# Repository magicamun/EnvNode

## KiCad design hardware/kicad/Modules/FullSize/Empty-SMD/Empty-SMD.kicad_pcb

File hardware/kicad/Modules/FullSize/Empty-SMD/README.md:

# EnvNode FullSize SMD Module Template

This KiCad project is the 38 mm × 64 mm starting point for a Revision 0.3 FullSize daughterboard with a bottom-mounted SMD module connector.

Copy the complete directory when starting a module. Do not add application circuitry to the template itself. Preserve the 2 × 7 connector mapping, connector axis 6.35 mm from the top edge, 2.7 mm M2.5 support holes at 27 mm and 59 mm, and the reference module-identification EEPROM circuit.

See the [module-interface hardware specification](../../../../../docs/EnvNode_Module_Interface_Hardware_Specification.md) and rerun ERC and DRC on every derived board.

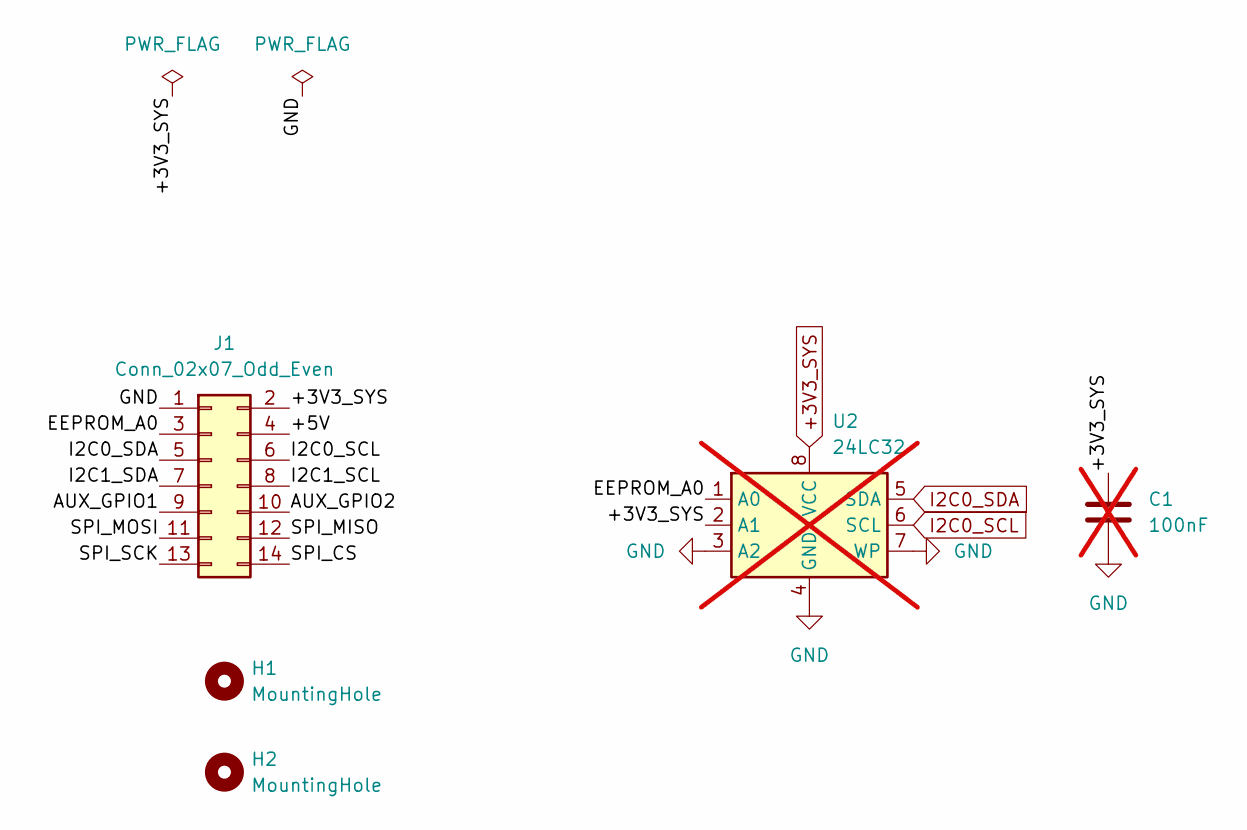
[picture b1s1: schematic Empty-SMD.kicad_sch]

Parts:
C1: 100nF; C_1206_3216Metric_Pad1.33x1.80mm_HandSolder; not fitted
H1, H2: MountingHole; MountingHole_2.7mm_M2.5_DIN965
J1: Conn_02x07_Odd_Even; J_Wurth_WR-PHD_61031421121
U2: 24LC32; SOIC-8_3.9x4.9mm_P1.27mm; not fitted

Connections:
+3V3_SYS: C1.1, J1.2, U2.2 (A1), U2.8 (VCC)
/+5V: J1.4
/AUX_GPIO1: J1.9
/AUX_GPIO2: J1.10
/EEPROM_A0: J1.3, U2.1 (A0)
/I2C1_SCL: J1.8
/I2C1_SDA: J1.7
/SPI_CS: J1.14
/SPI_MISO: J1.12
/SPI_MOSI: J1.11
/SPI_SCK: J1.13
GND: C1.2, J1.1, U2.3 (A2), U2.4 (GND), U2.7 (WP)
I2C0_SCL: J1.6, U2.6 (SCL)
I2C0_SDA: J1.5, U2.5 (SDA)

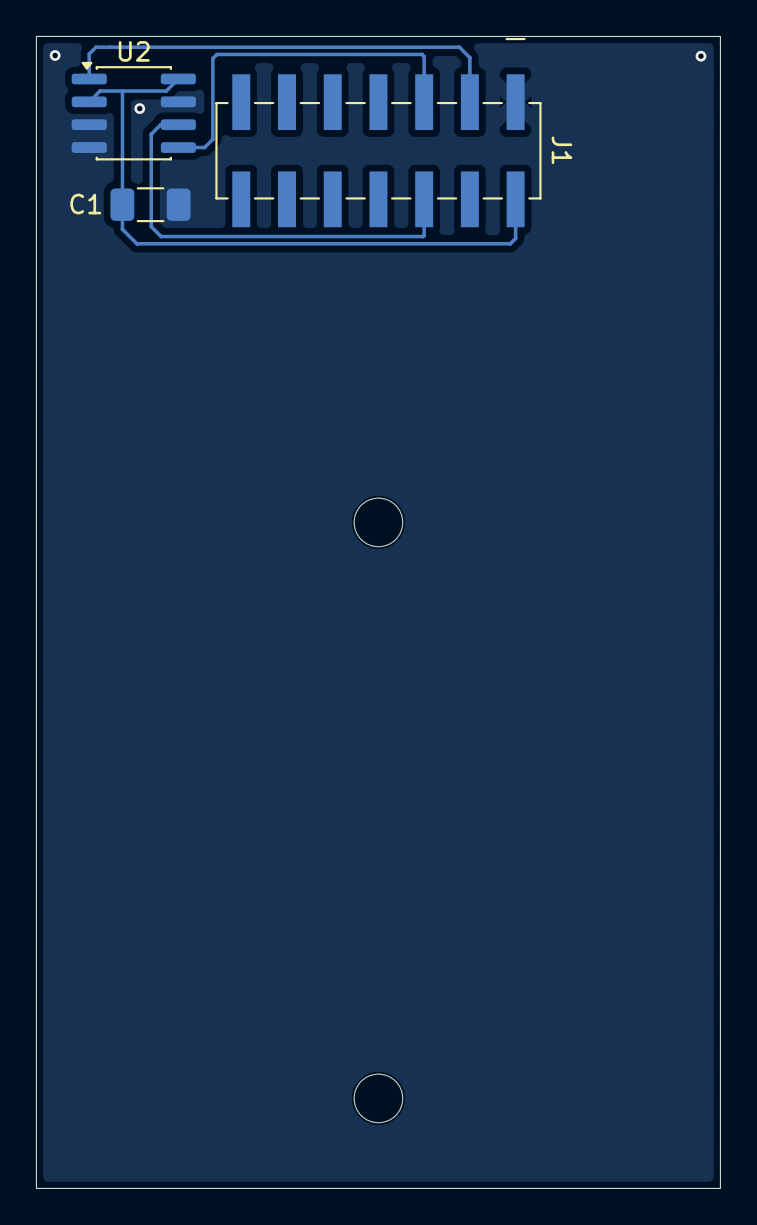
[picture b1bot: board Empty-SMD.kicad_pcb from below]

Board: 2 copper layers, 38.0 x 64.0 mm, 5 parts (3 on the bottom side), 5 nets.

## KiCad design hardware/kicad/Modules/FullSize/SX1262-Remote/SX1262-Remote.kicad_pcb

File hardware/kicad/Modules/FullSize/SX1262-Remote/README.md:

# EnvNode FullSize SX1262 Remote Radio Module

This KiCad 10 project implements a Revision 0.3 EnvNode FullSize radio daughterboard using the complete EBYTE E22-900M22S module. The E22 contains a Semtech SX1262 transceiver and supports the 868 MHz and 915 MHz ISM bands. The regional frequency and radio parameters are selected in firmware.

The board uses the 38 mm × 64 mm FullSize outline, bottom-mounted 2 × 7 THT module connector, two M2.5 support holes and the standard module-identification EEPROM circuit.

For supported operation, the module-identification EEPROM and its decoupling capacitor must be populated, and the EEPROM must contain a valid descriptor matching SX1262-Remote. Operation without module identification is not supported; the manual fallback described for DuoRelay and AnalogHydroPressure does not apply. This is a module requirement, not a statement that automatic radio-driver activation is already implemented.

## Host interface

The E22 is connected to the EnvNode host as follows:

| E22 signal | EnvNode signal | Function |
| --- | --- | --- |
| MOSI | SPI_MOSI | SPI data from host |
| MISO | SPI_MISO | SPI data to host |
| SCK | SPI_SCK | SPI clock |
| NSS | SPI_CS | Active-low SPI chip select |
| DIO1 | AUX_GPIO1 | Configurable radio interrupt |
| BUSY | AUX_GPIO2 | Radio busy indication |
| NRST | PCA9536 IO0 | Active-low hardware reset |

The PCA9536 GPIO expander is connected to I2C0. I2C1 remains unused by the radio circuitry. NRST and SPI_CS each have an external 10 kΩ pull-up to +3V3_SYS.

## RF-switch control

E22 DIO2 is connected directly to TXEN and must be enabled as the SX1262 RF-switch control output in firmware (`SetDIO2AsRfSwitchCtrl`). A BC847 NPN inverter generates the complementary RXEN signal:

- DIO2/TXEN high: TXEN high, RXEN low, transmit path enabled.
- DIO2/TXEN low: TXEN low, RXEN high, receive path enabled.

The inverter uses a 1 kΩ base resistor and a 10 kΩ RXEN pull-up. This hardware interlock avoids timing-dependent RF-switch control through an I2C GPIO expander.

## Power supply

The E22 and PCA9536 operate from +3V3_SYS. Place the 100 nF ceramic bypass capacitors close to their supply pins. The E22 additionally uses a local 22 µF ceramic bulk capacitor to support its approximately 120–140 mA transmit-current peaks.

## Antenna options

Use exactly one antenna connection:

1. Connect a suitable 868/915 MHz antenna or coaxial pigtail to the IPEX/U.FL-compatible socket on the E22. In this configuration E22 pin 21 (ANT) remains deliberately unconnected.
2. Connect a quarter-wave wire monopole to E22 pin 21. For 868 MHz, start with approximately 86 mm of straight insulated wire measured from the feed point. The carrier ground plane acts as the counterpoise. Keep the wire away from the PCB, batteries, cables and metal parts, and do not use the E22 IPEX socket simultaneously.

A wire antenna is installation-dependent and should be verified in the final enclosure. For production hardware, RF impedance and radiated performance should be measured and the antenna length or matching adjusted as required.

## Design notes

- Supply and logic levels are 3.3 V; do not apply 5 V to the E22.
- Connect every E22 GND pad to a low-impedance ground plane.
- Keep the radio and antenna away from switching regulators, fast clocks and high-current traces.
- Keep SPI traces short and route any connection from ANT pin 21 as a controlled 50 Ω RF path.
- Run KiCad ERC after schematic changes and DRC after PCB changes.

See the [module-interface hardware specification](../../../../../docs/EnvNode_Module_Interface_Hardware_Specification.md) for the authoritative EnvNode connector and mechanical requirements.

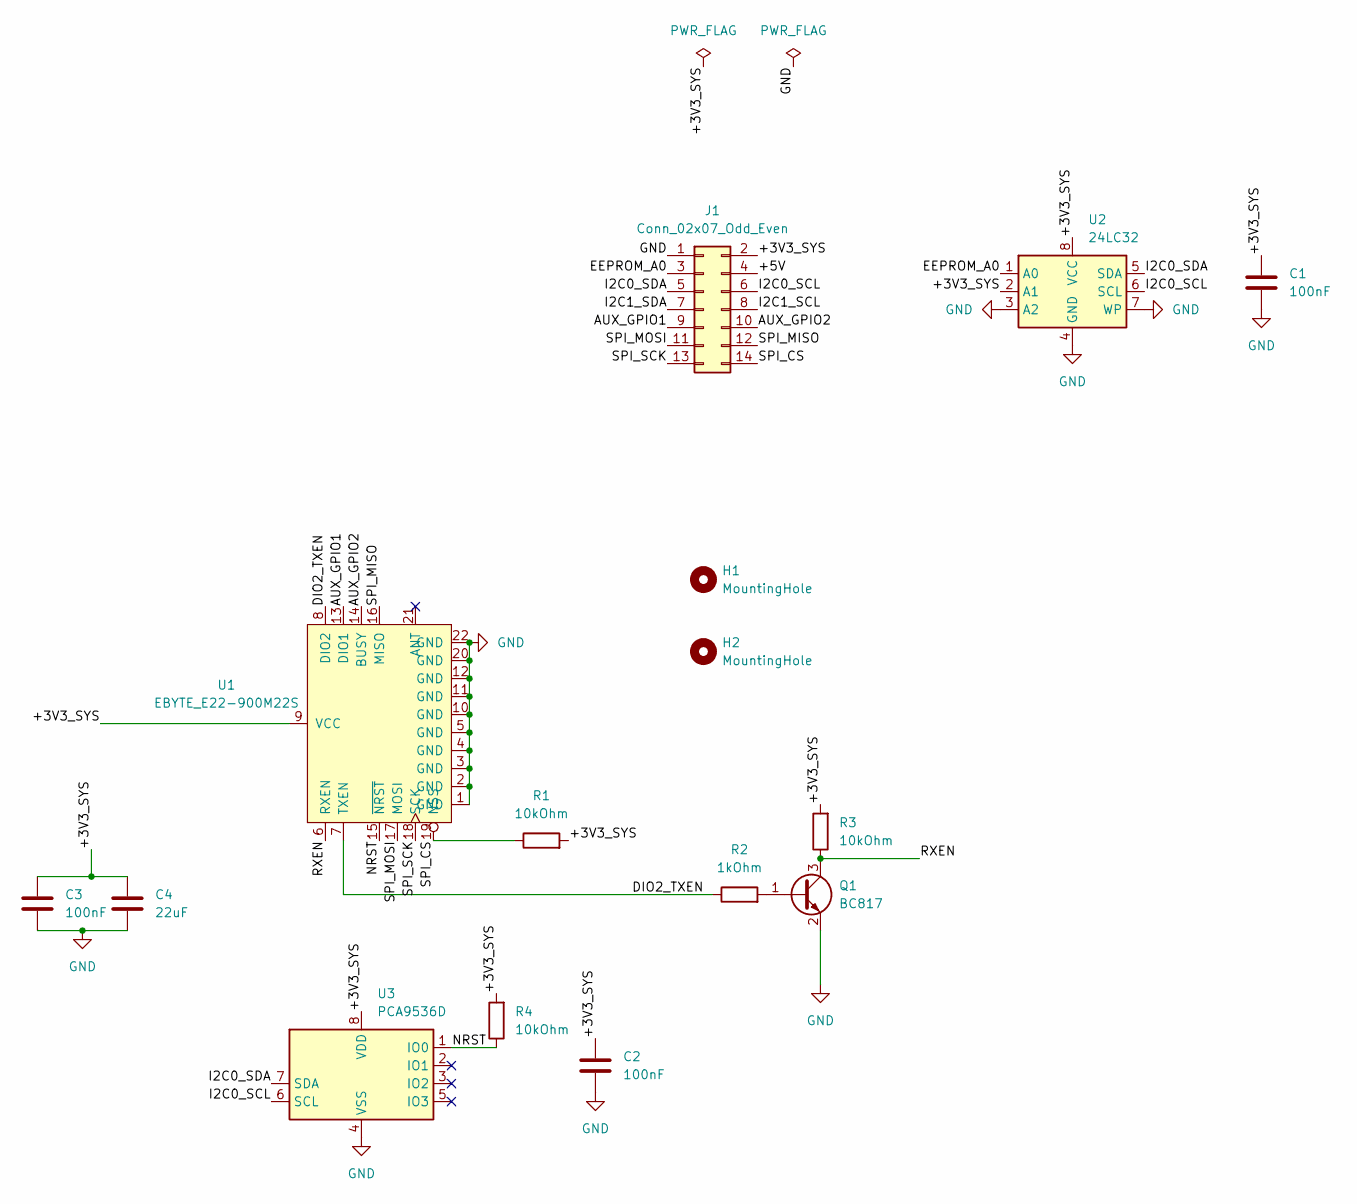
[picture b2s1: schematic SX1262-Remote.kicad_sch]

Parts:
C1, C2, C3: 100nF; C_1206_3216Metric_Pad1.33x1.80mm_HandSolder
C4: 22uF; C_1206_3216Metric_Pad1.33x1.80mm_HandSolder
H1, H2: MountingHole; MountingHole_2.7mm_M2.5_DIN965
J1: Conn_02x07_Odd_Even; PinHeader_2x07_P2.54mm_Vertical_Bottom
Q1: BC817; SOT-23
R1, R3, R4: 10kOhm; R_1206_3216Metric_Pad1.30x1.75mm_HandSolder
R2: 1kOhm; R_1206_3216Metric_Pad1.30x1.75mm_HandSolder
U1: EBYTE_E22-900M22S
U2: 24LC32; SOIC-8_3.9x4.9mm_P1.27mm
U3: PCA9536D; SOIC-8_3.9x4.9mm_P1.27mm

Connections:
/+3V3_SYS: C1.1, C2.1, C3.1, C4.1, J1.2, R1.2, R3.2, R4.2, U1.9 (VCC), U2.2 (A1), U2.8 (VCC), U3.8 (VDD)
/+5V: J1.4
/AUX_GPIO1: J1.9, U1.13 (DIO1)
/AUX_GPIO2: J1.10, U1.14 (BUSY)
/DIO2_TXEN: R2.1, U1.7 (TXEN), U1.8 (DIO2)
/EEPROM_A0: J1.3, U2.1 (A0)
/I2C0_SCL: J1.6, U2.6 (SCL), U3.6 (SCL)
/I2C0_SDA: J1.5, U2.5 (SDA), U3.7 (SDA)
/I2C1_SCL: J1.8
/I2C1_SDA: J1.7
/NRST: R4.1, U1.15 (~NRST), U3.1 (IO0)
/RXEN: Q1.3 (C), R3.1, U1.6 (RXEN)
/SPI_CS: J1.14, R1.1, U1.19 (NSS)
/SPI_MISO: J1.12, U1.16 (MISO)
/SPI_MOSI: J1.11, U1.17 (MOSI)
/SPI_SCK: J1.13, U1.18 (SCK)
GND: C1.2, C2.2, C3.2, C4.2, J1.1, Q1.2 (E), U1.1 (GND), U1.2 (GND), U1.3 (GND), U1.4 (GND), U1.5 (GND), U1.10 (GND), U1.11 (GND), U1.12 (GND), U1.20 (GND), U1.22 (GND), U2.3 (A2), U2.4 (GND), U2.7 (WP), U3.4 (VSS)
unnamed: Q1.1 (B), R2.2

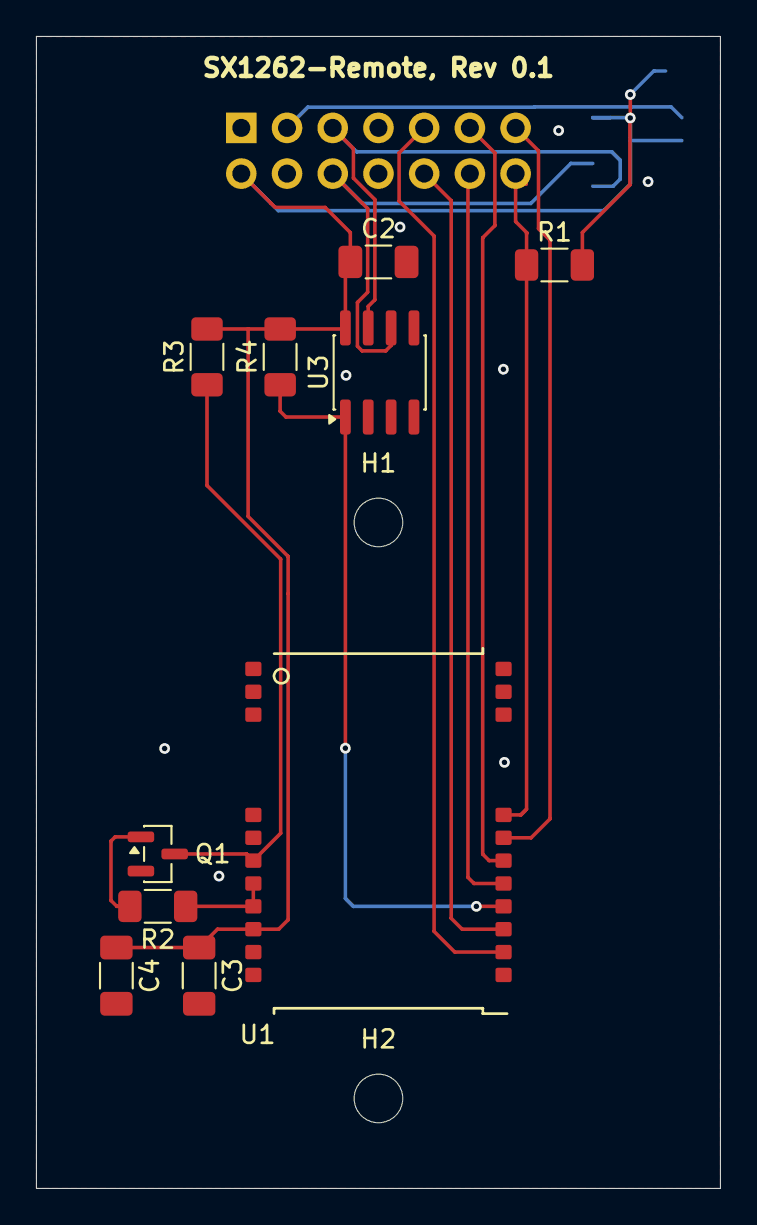
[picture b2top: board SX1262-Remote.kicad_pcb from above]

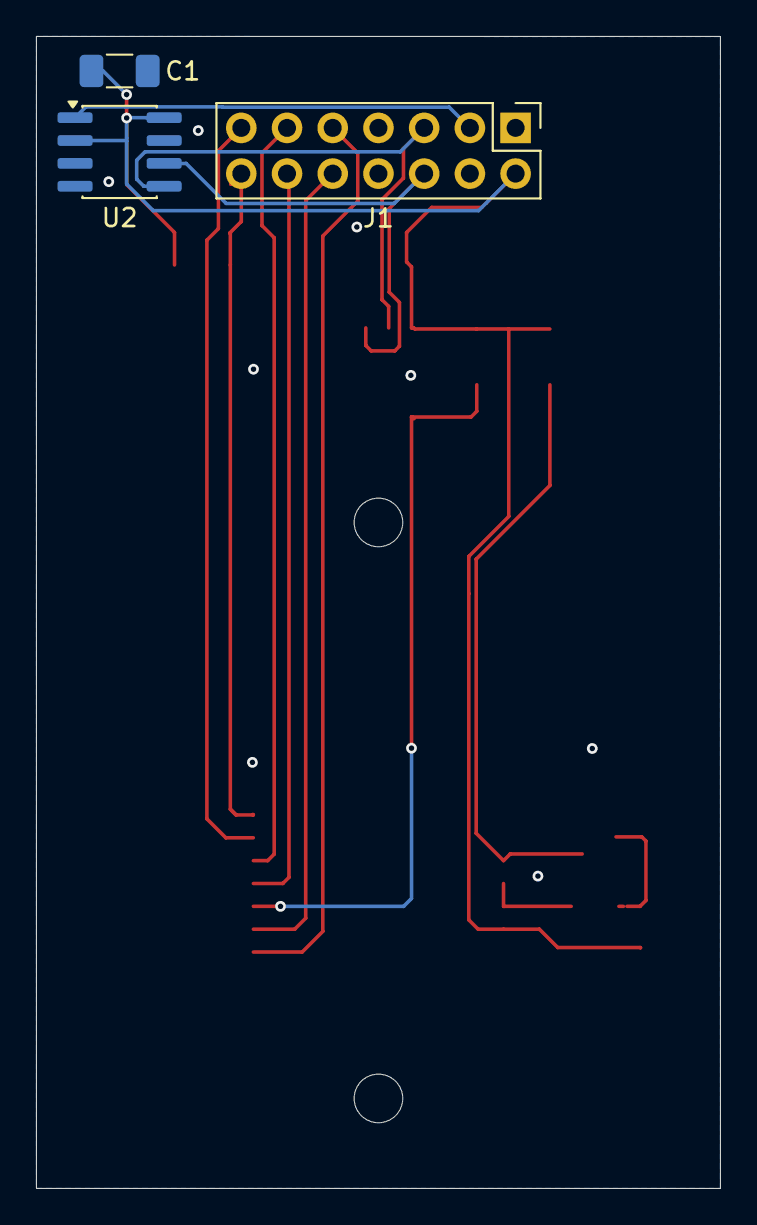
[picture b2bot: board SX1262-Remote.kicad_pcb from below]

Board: 2 copper layers, 38.0 x 64.0 mm, 15 parts (3 on the bottom side), 15 nets.
